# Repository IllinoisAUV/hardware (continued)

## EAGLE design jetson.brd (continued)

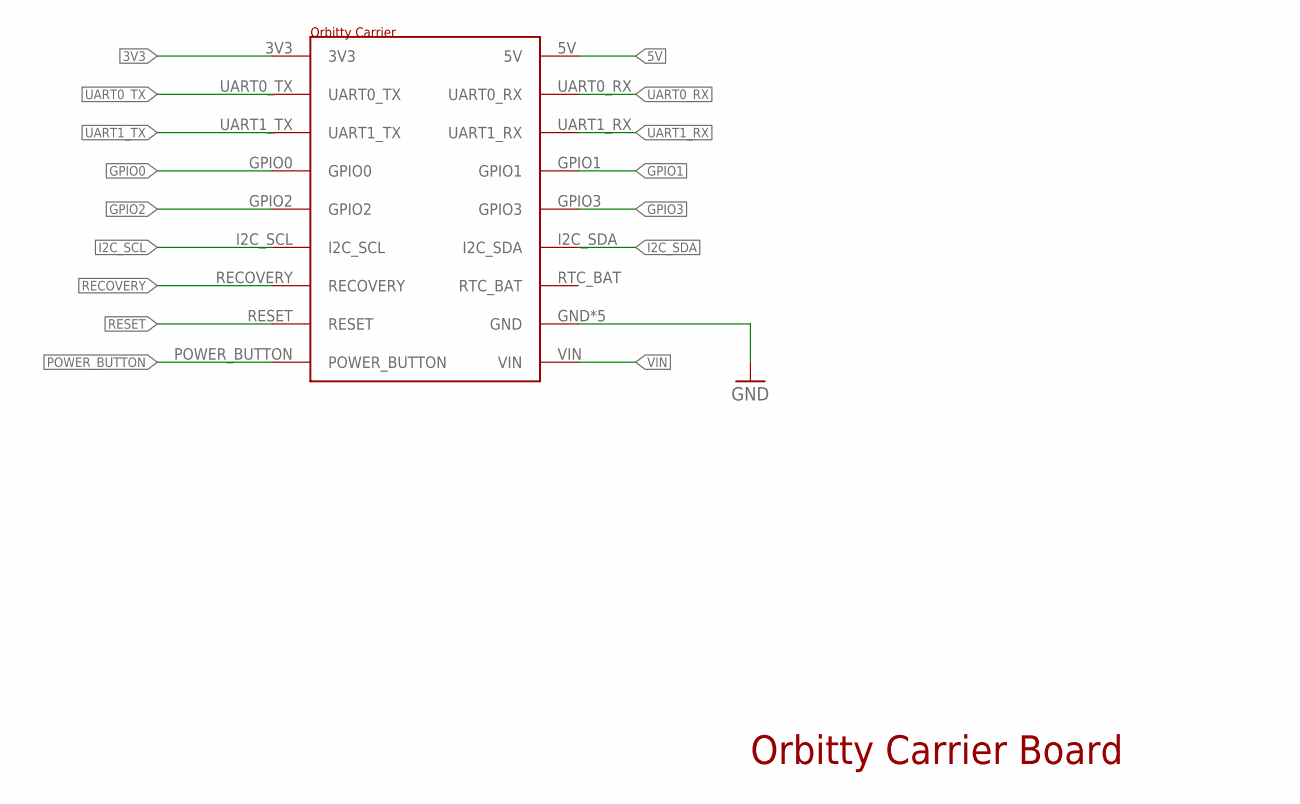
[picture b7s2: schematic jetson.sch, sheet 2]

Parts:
U$1: ORBITTY_CARRIER

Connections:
3V3: U$1.3V3
5V: U$1.5V
GND: U$1.GND, U$1.GND1 (GND), U$1.GND2 (GND), U$1.GND3 (GND), U$1.GND4 (GND); also elsewhere on the board
GPIO0: U$1.GPIO0; also elsewhere on the board
GPIO1: U$1.GPIO1; also elsewhere on the board
GPIO2: U$1.GPIO2; also elsewhere on the board
GPIO3: U$1.GPIO3; also elsewhere on the board
I2C_SCL: U$1.I2C_SCL; also elsewhere on the board
I2C_SDA: U$1.I2C_SDA; also elsewhere on the board
POWER_BUTTON: U$1.POWER_BUTTON; also elsewhere on the board
RECOVERY: U$1.RECOVERY; also elsewhere on the board
RESET: U$1.RESET; also elsewhere on the board
UART0_RX: U$1.UART0_RX; also elsewhere on the board
UART0_TX: U$1.UART0_TX; also elsewhere on the board
UART1_RX: U$1.UART1_RX; also elsewhere on the board
UART1_TX: U$1.UART1_TX; also elsewhere on the board
VIN: U$1.VIN; also elsewhere on the board

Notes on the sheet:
Orbitty Carrier Board

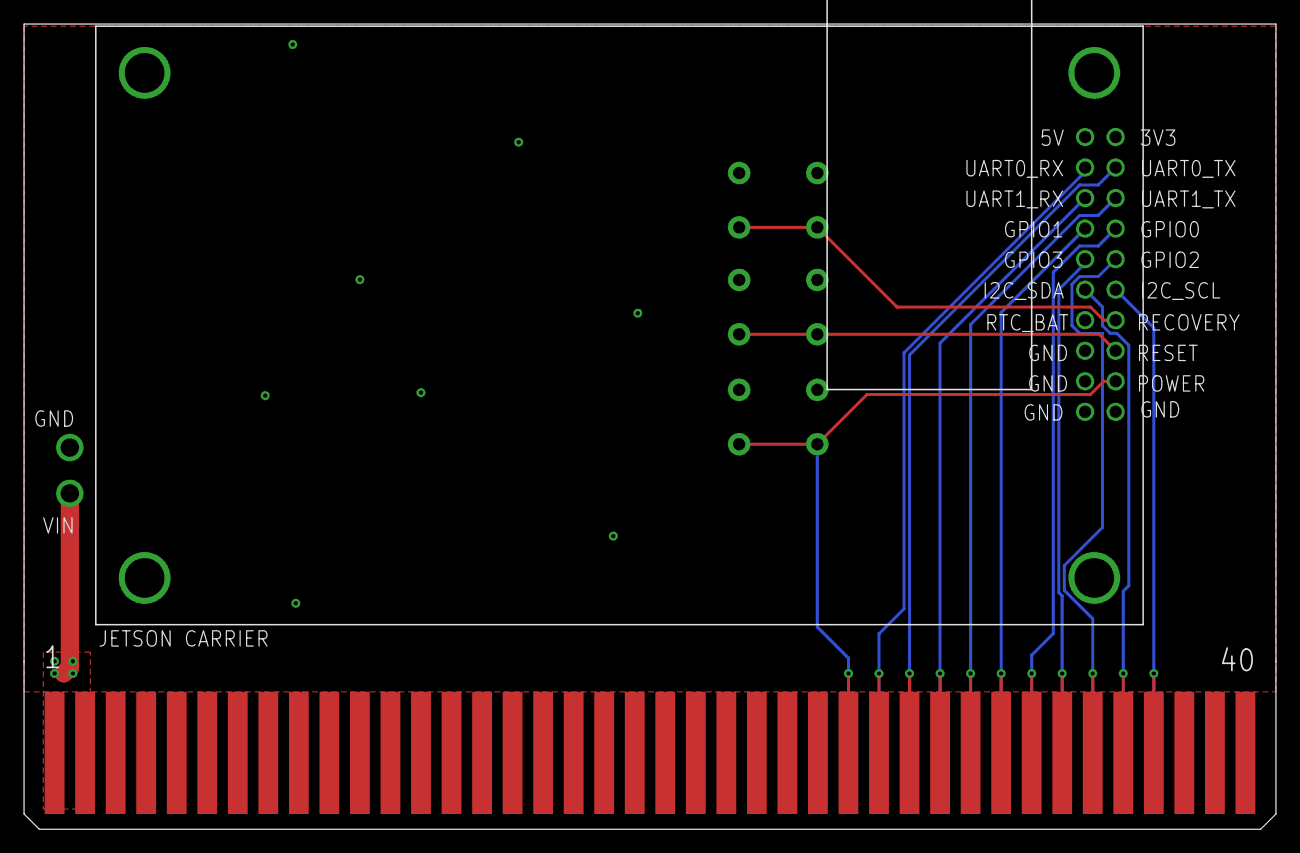
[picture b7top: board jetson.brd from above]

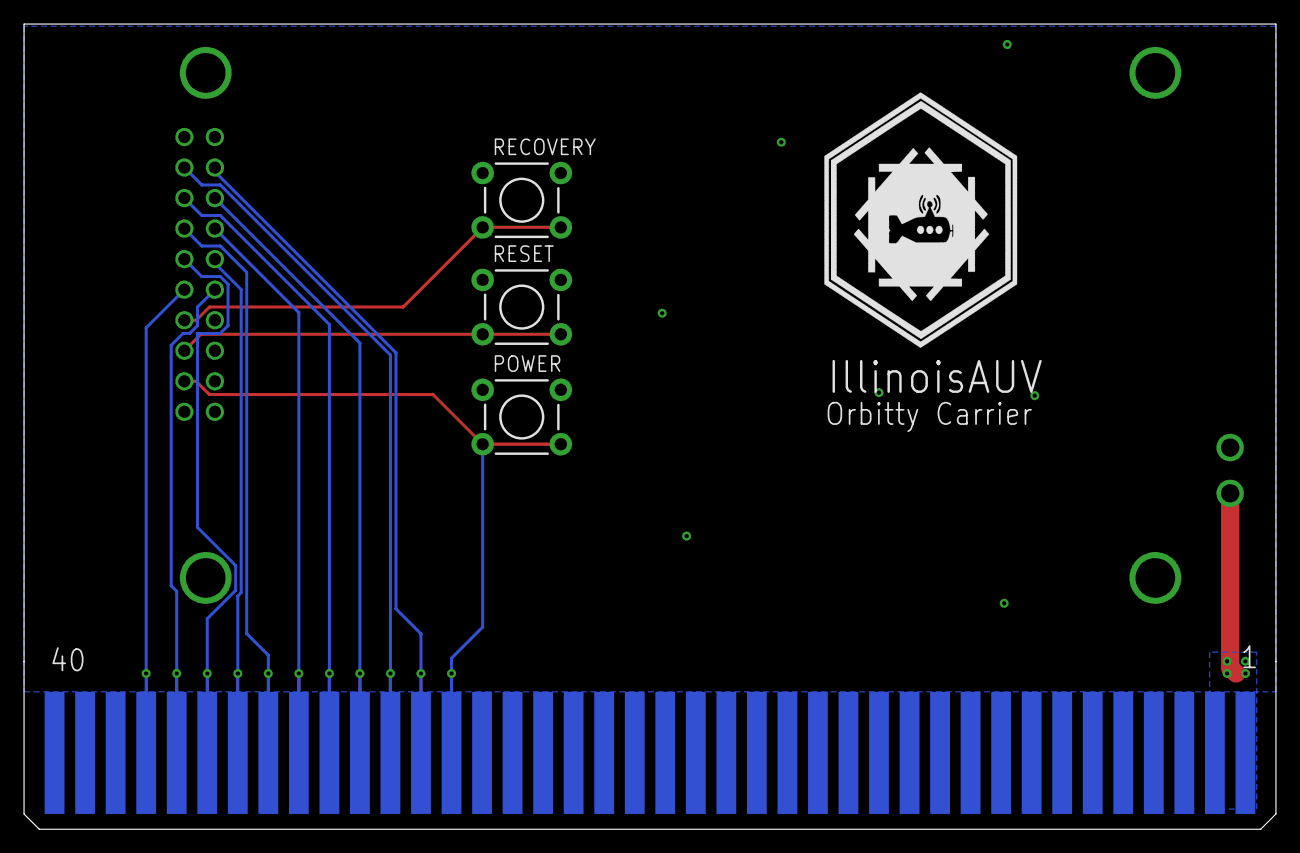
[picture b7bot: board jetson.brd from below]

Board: 2 copper layers, 104.1 x 67.0 mm, 6 parts (4 on the bottom side), 15 nets.

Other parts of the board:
U$2: ILLINOISAUV

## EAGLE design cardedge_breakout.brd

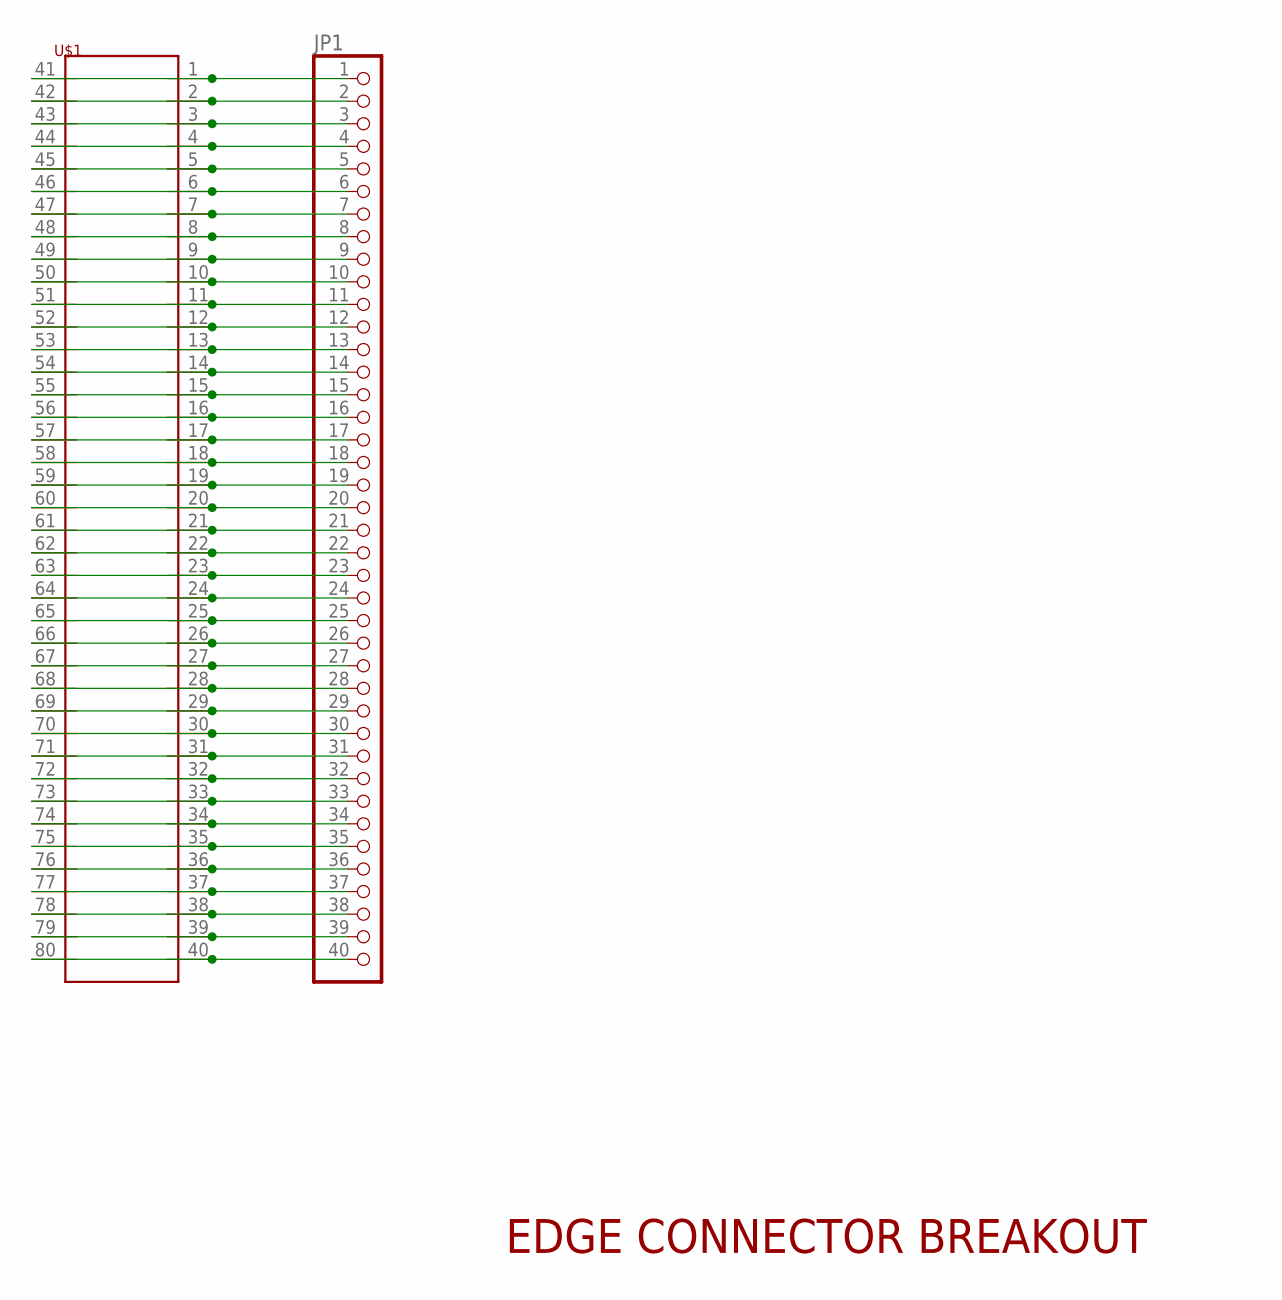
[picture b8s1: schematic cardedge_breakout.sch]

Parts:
JP1: PINHD-1X40; 1X40
U$1: 80-PIN-CARD-EDGE

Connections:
unnamed: JP1.1, U$1.1, U$1.41
unnamed: JP1.2, U$1.2, U$1.42
unnamed: JP1.3, U$1.3, U$1.43
unnamed: JP1.4, U$1.4, U$1.44
unnamed: JP1.5, U$1.5, U$1.45
unnamed: JP1.6, U$1.6, U$1.46
unnamed: JP1.7, U$1.7, U$1.47
unnamed: JP1.8, U$1.8, U$1.48
unnamed: JP1.9, U$1.9, U$1.49
unnamed: JP1.10, U$1.10, U$1.50
unnamed: JP1.11, U$1.11, U$1.51
unnamed: JP1.12, U$1.12, U$1.52
unnamed: JP1.13, U$1.13, U$1.53
unnamed: JP1.14, U$1.14, U$1.54
unnamed: JP1.15, U$1.15, U$1.55
unnamed: JP1.16, U$1.16, U$1.56
unnamed: JP1.17, U$1.17, U$1.57
unnamed: JP1.18, U$1.18, U$1.58
unnamed: JP1.19, U$1.19, U$1.59
unnamed: JP1.20, U$1.20, U$1.60
unnamed: JP1.21, U$1.21, U$1.61
unnamed: JP1.22, U$1.22, U$1.62
unnamed: JP1.23, U$1.23, U$1.63
unnamed: JP1.24, U$1.24, U$1.64
unnamed: JP1.25, U$1.25, U$1.65
unnamed: JP1.26, U$1.26, U$1.66
unnamed: JP1.27, U$1.27, U$1.67
unnamed: JP1.28, U$1.28, U$1.68
unnamed: JP1.29, U$1.29, U$1.69
unnamed: JP1.30, U$1.30, U$1.70
unnamed: JP1.31, U$1.31, U$1.71
unnamed: JP1.32, U$1.32, U$1.72
unnamed: JP1.33, U$1.33, U$1.73
unnamed: JP1.34, U$1.34, U$1.74
unnamed: JP1.35, U$1.35, U$1.75
unnamed: JP1.36, U$1.36, U$1.76
unnamed: JP1.37, U$1.37, U$1.77
unnamed: JP1.38, U$1.38, U$1.78
unnamed: JP1.39, U$1.39, U$1.79
unnamed: JP1.40, U$1.40, U$1.80

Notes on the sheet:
EDGE CONNECTOR BREAKOUT

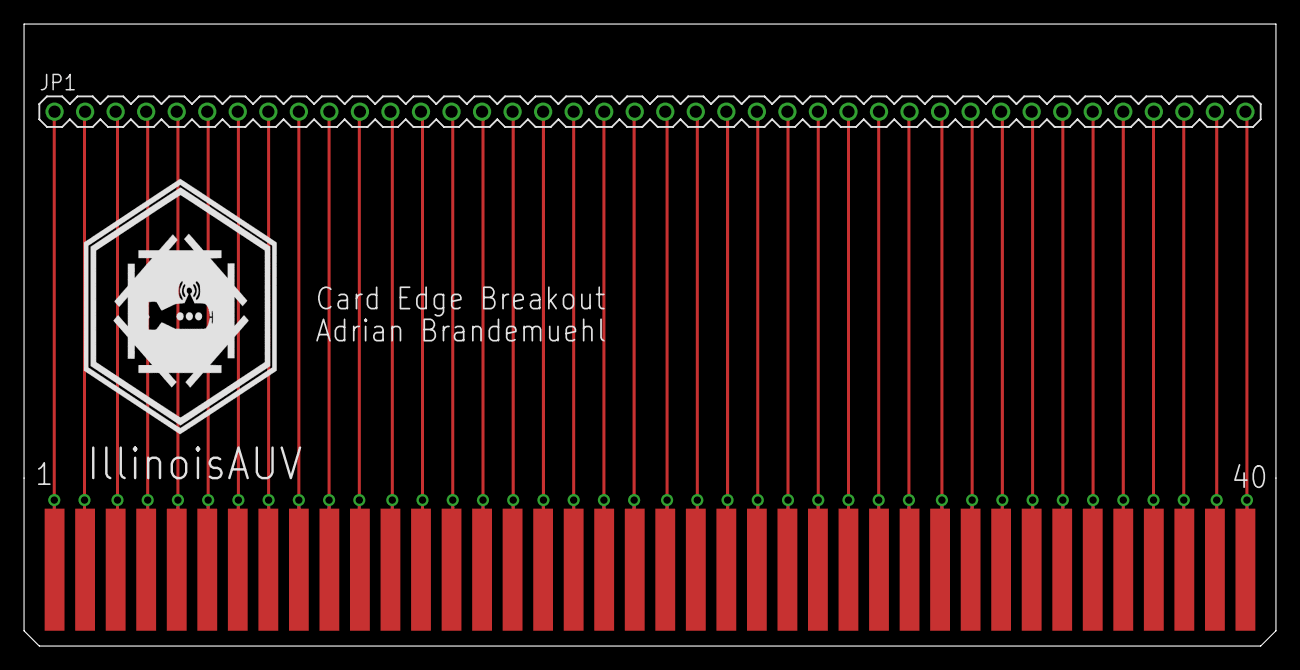
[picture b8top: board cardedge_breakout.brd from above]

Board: 2 copper layers, 104.1 x 51.7 mm, 3 parts (0 on the bottom side), 40 nets.

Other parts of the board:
U$2: ILLINOISAUV

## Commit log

2017-11-05 Initial commit
    Includes pixhawk carrier board
2017-11-05 Added Speed controller schematic
2017-11-12 Create Jetson Carrier for Orbitty Carrier
2017-11-12 Add breakout card edge board
2017-11-12 Add breakouts for card edge connectors
2017-11-12 Add numbering to board
    I've realized that we have to prevent people from plugging in boards
    backwards, so I've added visual markers of what pin is what
2017-12-27 Added MOSFETs to speed controllers
2018-01-13 Redid ESC boards
2018-02-04 Start pixhawk board redesign
2018-02-11 Redesigned PixHawk Board
2018-02-18 Updates and fixes
2018-02-25 Move jetson to the backplane
2018-04-07 Update backplane
2018-04-07 Add pcbway cam file
2018-04-07 Add XT60 connector
2018-04-07 Depth sensor I2C
2018-04-07 Add pixhawk connectors
2018-04-07 Add RS232-UART converter
2018-04-07 Add jetson - converter uart connection
2018-04-08 Buck Converter Power Board
    Step down to 5V and 3.3V
2018-04-15 ESC Board
    Features:
    * 8 ESC's
    * XT60 battery connector P-Channel mosfets for kill switch
    * Hall effect kill switch
    * LED Kill switch indicators
2018-04-15 Add AHRS8P breakout
    Connects usb to AHRS8P
    * Uses FT232R for usb to UART connection
2018-04-16 Changed Optocoupler circuit
2018-04-29 Redid PWM and moved silkscreen for the XT-60
2018-05-16 Make pads on ss4 connector longer
2018-05-16 Add auv logo
2018-05-21 Changed board to not have anything within a 5 inch diameter on the back side
2018-05-21 Fix xt60 connector
2018-05-21 Fix silkscreen
2018-05-21 Redo routing
2018-05-21 Fix DRC errors
2018-05-21 Add another hall effect and fix resistor value
2018-05-21 Remove outer circle. Add logo
2018-05-21 ld1117
2018-05-21 LDO power board
2018-05-21 Add cap values
2018-10-27 cleaning up for 2018
2018-10-27 adding pixhawk carrier board
2018-10-27 updated library"
